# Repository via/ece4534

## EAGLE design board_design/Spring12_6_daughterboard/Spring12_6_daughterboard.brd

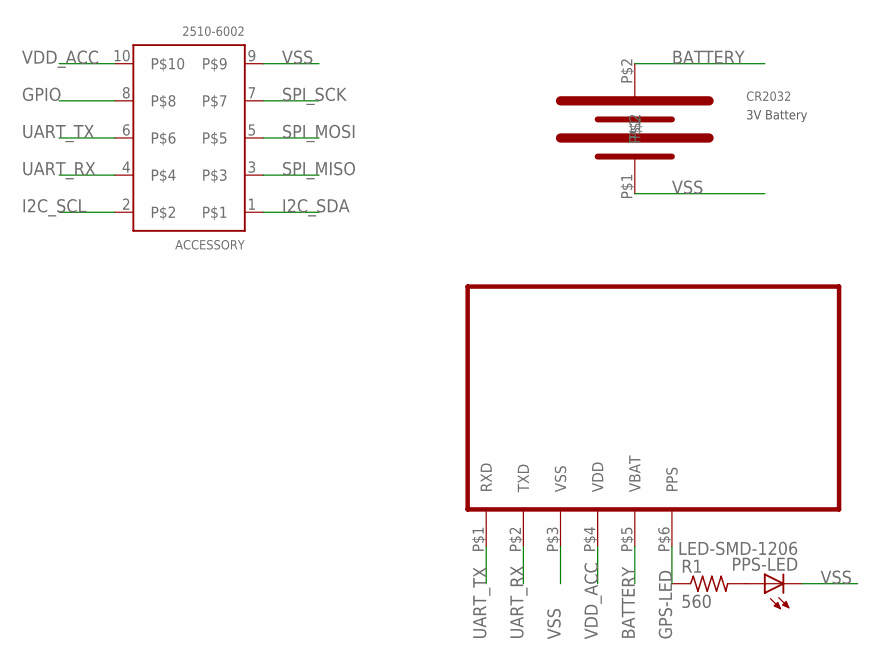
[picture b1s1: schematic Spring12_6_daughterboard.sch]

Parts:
ACCESSORY: 2510-6002
PPS-LED: LED-SMD-1206; LED1206
R1: 560; R1206
U$1: 796136-1-CR2302_HOLDER; 796136-1-CR2032_HOLDER
U$3: GPS-UP501

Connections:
BATTERY: U$1.P$2, U$3.P$5 (VBAT)
GPIO: ACCESSORY.8
GPS-LED: R1.1, U$3.P$6 (PPS)
I2C_SCL: ACCESSORY.2
I2C_SDA: ACCESSORY.1
unnamed: PPS-LED.A, R1.2
SPI_MISO: ACCESSORY.3
SPI_MOSI: ACCESSORY.5
SPI_SCK: ACCESSORY.7
UART_RX: ACCESSORY.4, U$3.P$2 (TXD)
UART_TX: ACCESSORY.6, U$3.P$1 (RXD)
VDD_ACC: ACCESSORY.10, U$3.P$4 (VDD)
VSS: ACCESSORY.9, PPS-LED.C, U$1.P$1, U$3.P$3 (VSS)

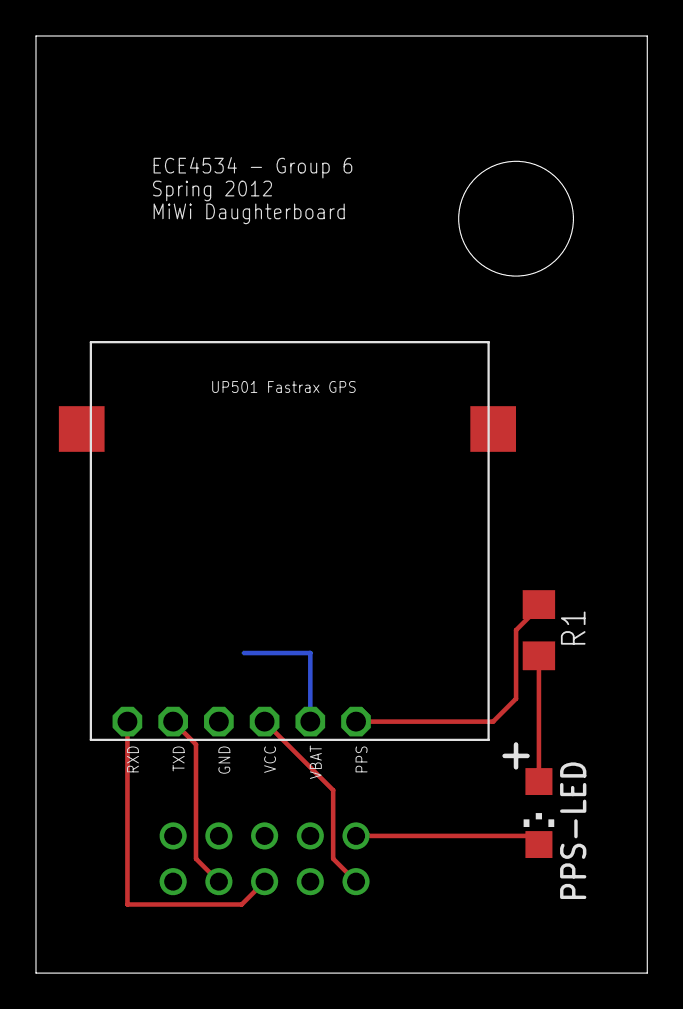
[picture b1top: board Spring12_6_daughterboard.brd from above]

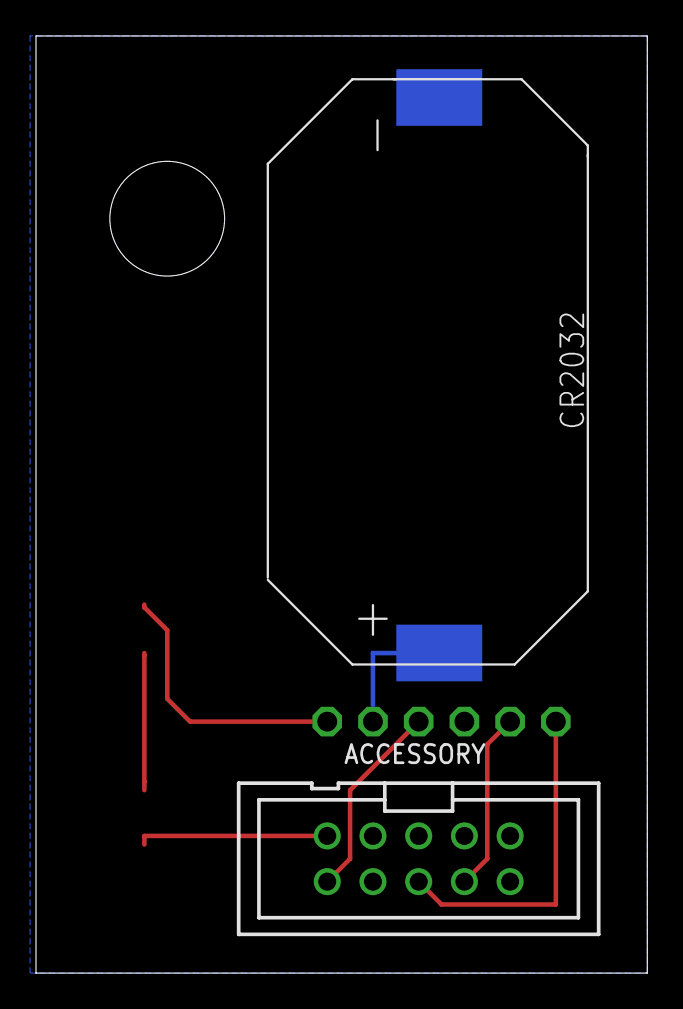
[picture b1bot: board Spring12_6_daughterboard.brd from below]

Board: 2 copper layers, 34.0 x 52.1 mm, 5 parts (2 on the bottom side), 7 nets.

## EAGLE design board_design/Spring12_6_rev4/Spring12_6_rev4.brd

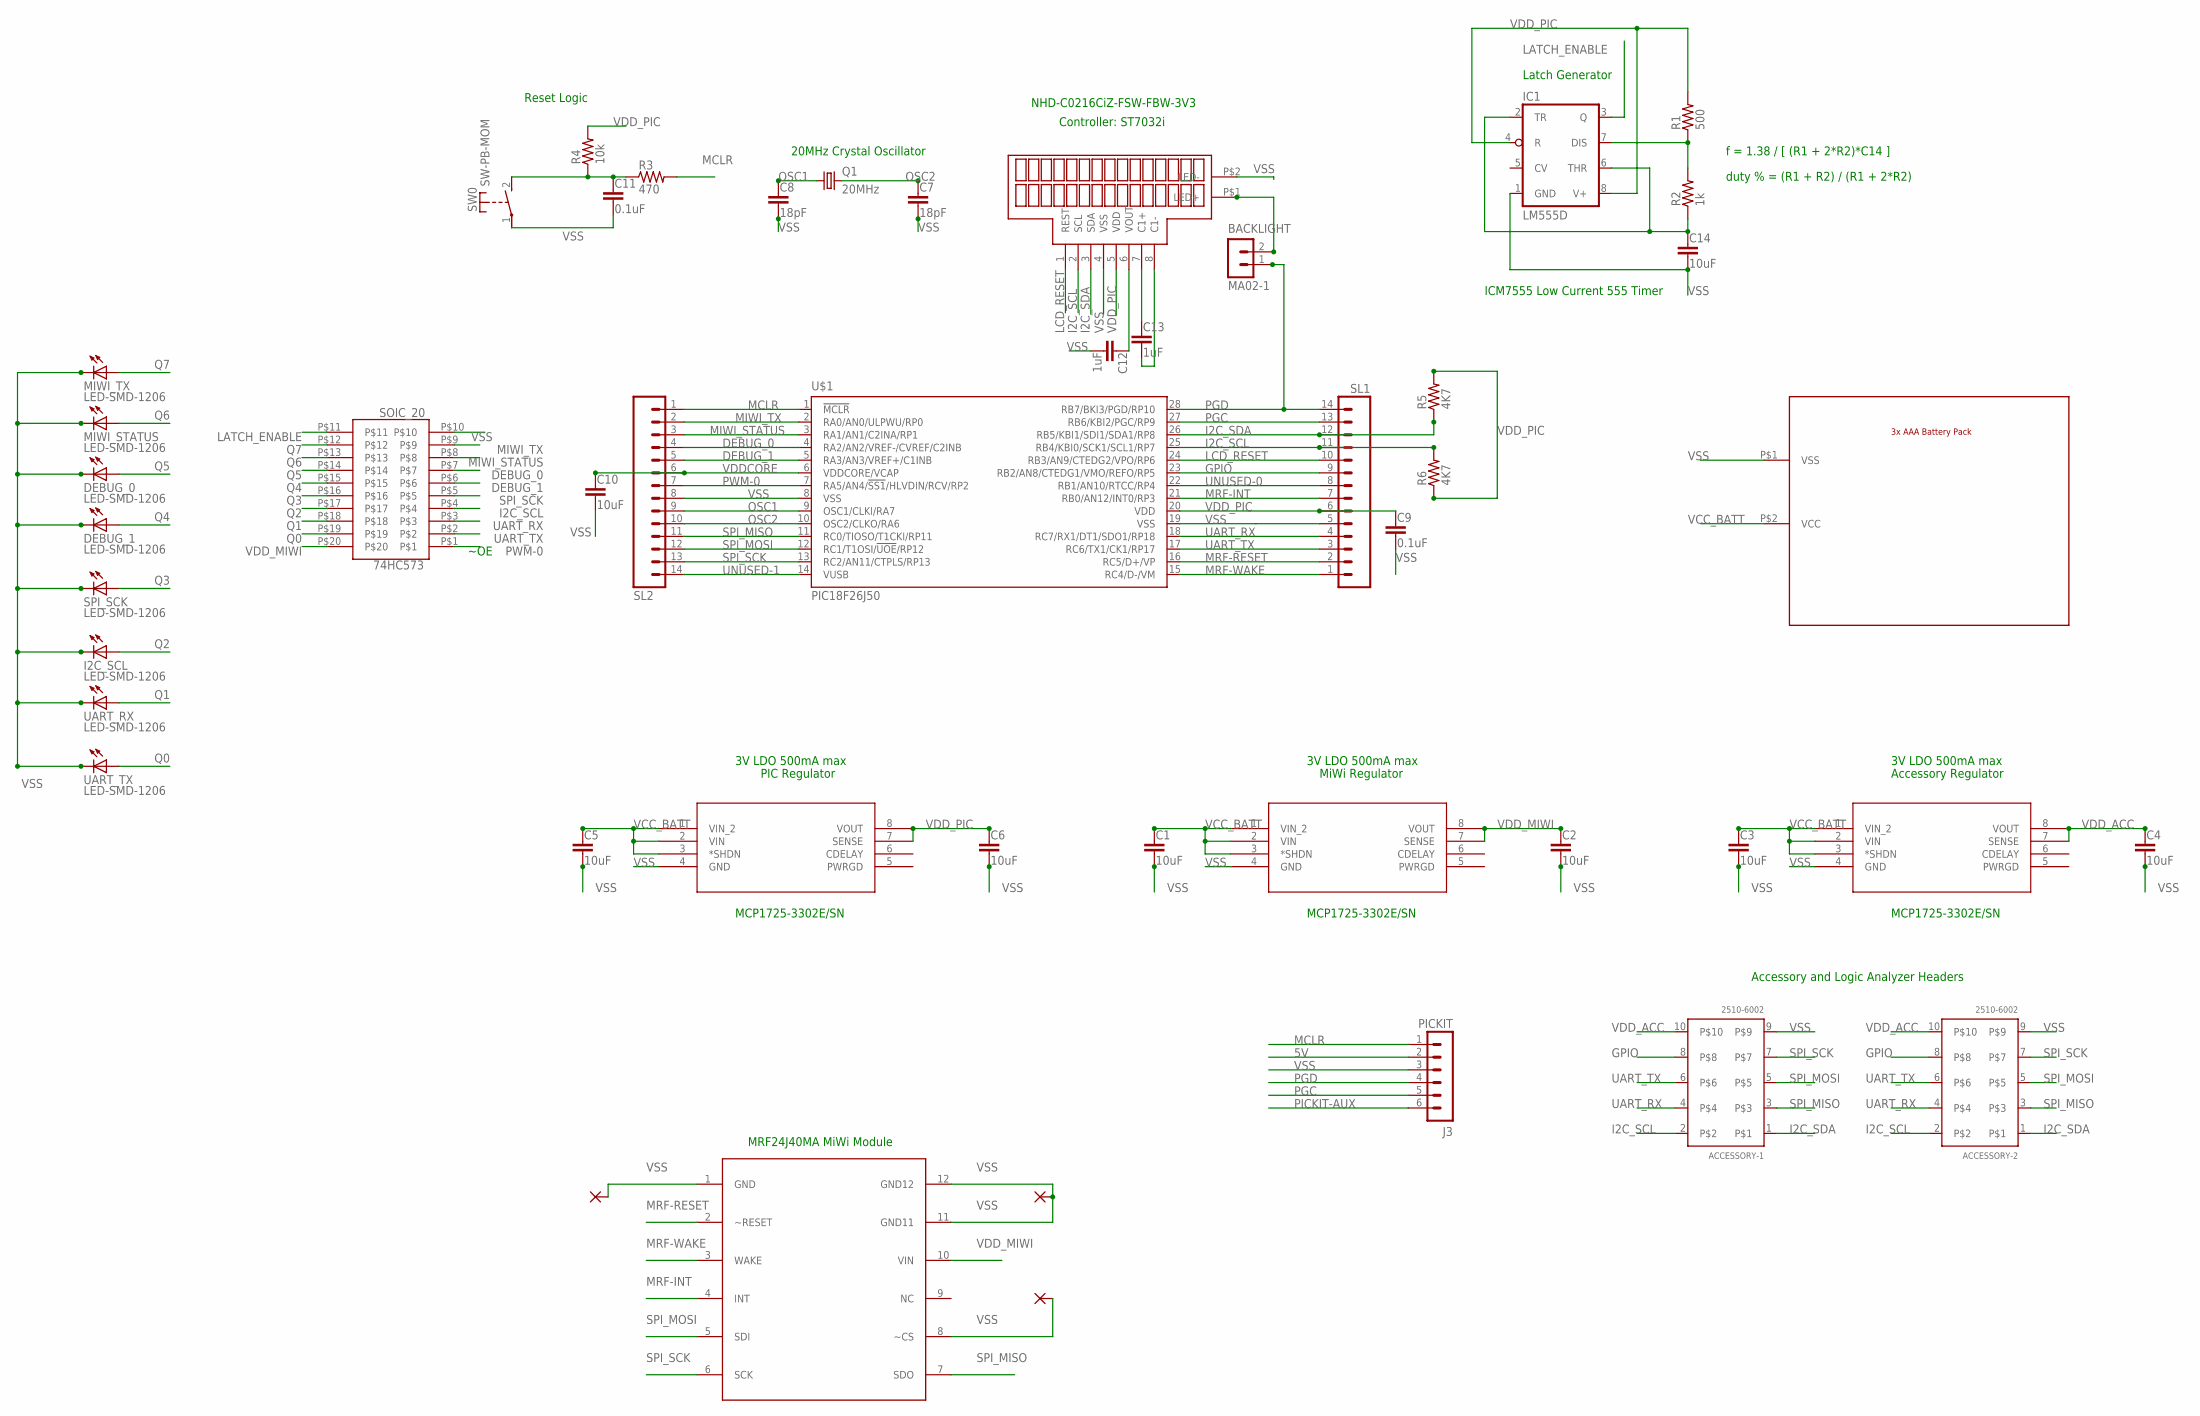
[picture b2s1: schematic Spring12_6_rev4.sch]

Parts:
74HC573: SOIC_20; SO20W
ACCESSORY-1, ACCESSORY-2: 2510-6002
BACKLIGHT: MA02-1
BATT0: 2479-BATTERY
C1, C2, C3, C4, C5, C6, C14: 10uF; C2.5-5
C7: 18pF; C2.5-5
C8: 18pF; C2.5-5; DIGIKEY 490-3632-ND
C9, C11: 0.1uF; C2.5-5; DIGIKEY 490-3632-ND
C10: 10uF; C2.5-5; DIGIKEY 490-3632-ND
C12, C13: 1uF; C2.5-5; DIGIKEY 490-3632-ND
DEBUG_0, DEBUG_1: LED-SMD-1206; LED1206
I2C_SCL: LED-SMD-1206; LED1206
IC1: LM555D; SO08
J3: PICKIT; MA06-1
MIWI_STATUS: LED-SMD-1206; LED1206
MIWI_TX: LED-SMD-1206; LED1206
Q1: 20MHz; HC49U-V; DIGIKEY XC1723-ND
R1: 500; R1206
R2: 1k; R1206
R3: 470; R1206
R4: 10k; R1206
R5, R6: 4K7; R1206
REG0, REG1, REG2: MCP1725-XXXXX/SN; SOIC8-N_MC
RF0: MRF24J40MA; PCB12
SL1, SL2: M14; 14P
SPI_SCK: LED-SMD-1206; LED1206
SW0: SW-PB-MOM; SW-MOM-PB
U$1: PIC18F26J50; DIL28-3
U$2: NHD-C0216CIZ-FN-FBW-3V; SIL8-1.5
U$18, U$19, U$20: VIA
UART_RX: LED-SMD-1206; LED1206
UART_TX: LED-SMD-1206; LED1206

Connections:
5V: J3.2
DEBUG_0: 74HC573.P$7, SL2.4, U$1.4 (RA2/AN2/VREF-/CVREF/C2INB)
DEBUG_1: 74HC573.P$6, SL2.5, U$1.5 (RA3/AN3/VREF+/C1INB)
GPIO: ACCESSORY-1.8, ACCESSORY-2.8, SL1.9, U$1.23 (RB2/AN8/CTEDG1/VMO/REFO/RP5)
I2C_SCL: 74HC573.P$4, ACCESSORY-1.2, ACCESSORY-2.2, R6.2, SL1.11, U$1.25 (RB4/KBI0/SCK1/SCL1/RP7), U$2.2 (SCL)
I2C_SDA: ACCESSORY-1.1, ACCESSORY-2.1, R5.1, SL1.12, U$1.26 (RB5/KBI1/SDI1/SDA1/RP8), U$2.3 (SDA)
LATCH_ENABLE: 74HC573.P$11, IC1.3 (Q)
LCD_RESET: SL1.10, U$1.24 (RB3/AN9/CTEDG2/VPO/RP6), U$2.1 (REST)
MCLR: J3.1, R3.2, SL2.1, U$1.1 (!MCLR)
MIWI_STATUS: 74HC573.P$8, SL2.3, U$1.3 (RA1/AN1/C2INA/RP1)
MIWI_TX: 74HC573.P$9, SL2.2, U$1.2 (RA0/AN0/ULPWU/RP0)
MRF-INT: RF0.4 (INT), SL1.7, U$1.21 (RB0/AN12/INT0/RP3)
MRF-RESET: RF0.2 (~RESET), SL1.2, U$1.16 (RC5/D+/VP)
MRF-WAKE: RF0.3 (WAKE), SL1.1, U$1.15 (RC4/D-/VM)
unnamed: BACKLIGHT.2, U$2.P$1 (LED+)
unnamed: IC1.7 (DIS), R1.1, R2.2
unnamed: C14.1, IC1.2 (TR), IC1.6 (THR), R2.1
unnamed: C11.1, R3.1, R4.1, SW0.2 (S)
unnamed: C12.1, U$2.6 (VOUT)
unnamed: C13.1, U$2.7 (C1+)
unnamed: C13.2, U$2.8 (C1-)
OSC1: C8.1, Q1.1, SL2.9, U$1.9 (OSC1/CLKI/RA7)
OSC2: C7.1, Q1.2, SL2.10, U$1.10 (OSC2/CLKO/RA6)
PGC: J3.5, SL1.13, U$1.27 (RB6/KBI2/PGC/RP9)
PGD: BACKLIGHT.1, J3.4, SL1.14, U$1.28 (RB7/BKI3/PGD/RP10)
PICKIT-AUX: J3.6
PWM-0: 74HC573.P$1, SL2.7, U$1.7 (RA5/AN4/!SS1!/HLVDIN/RCV/RP2)
Q0: 74HC573.P$19, UART_TX.A
Q1: 74HC573.P$18, UART_RX.A
Q2: 74HC573.P$17, I2C_SCL.A
Q3: 74HC573.P$16, SPI_SCK.A
Q4: 74HC573.P$15, DEBUG_1.A
Q5: 74HC573.P$14, DEBUG_0.A
Q6: 74HC573.P$13, MIWI_STATUS.A
Q7: 74HC573.P$12, MIWI_TX.A
SPI_MISO: ACCESSORY-1.3, ACCESSORY-2.3, RF0.7 (SDO), SL2.11, U$1.11 (RC0/TIOSO/T1CKI/RP11)
SPI_MOSI: ACCESSORY-1.5, ACCESSORY-2.5, RF0.5 (SDI), SL2.12, U$1.12 (RC1/T1OSI/!UOE!/RP12)
SPI_SCK: 74HC573.P$5, ACCESSORY-1.7, ACCESSORY-2.7, RF0.6 (SCK), SL2.13, U$1.13 (RC2/AN11/CTPLS/RP13)
UART_RX: 74HC573.P$3, ACCESSORY-1.4, ACCESSORY-2.4, SL1.4, U$1.18 (RC7/RX1/DT1/SDO1/RP18)
UART_TX: 74HC573.P$2, ACCESSORY-1.6, ACCESSORY-2.6, SL1.3, U$1.17 (RC6/TX1/CK1/RP17)
UNUSED-0: SL1.8, U$1.22 (RB1/AN10/RTCC/RP4)
UNUSED-1: SL2.14, U$1.14 (VUSB)
VCC_BATT: BATT0.P$2 (VCC), C1.1, C3.1, C5.1, REG0.1 (VIN_2), REG0.2 (VIN), REG0.3 (*SHDN), REG1.1 (VIN_2), REG1.2 (VIN), REG1.3 (*SHDN), REG2.1 (VIN_2), REG2.2 (VIN), REG2.3 (*SHDN)
VDDCORE: C10.1, SL2.6, U$1.6 (VDDCORE/VCAP)
VDD_ACC: ACCESSORY-1.10, ACCESSORY-2.10, C4.1, REG2.7 (SENSE), REG2.8 (VOUT)
VDD_MIWI: 74HC573.P$20, C2.1, REG1.7 (SENSE), REG1.8 (VOUT), RF0.10 (VIN)
VDD_PIC: C6.1, C9.1, IC1.4 (R), IC1.8 (V+), R1.2, R4.2, R5.2, R6.1, REG0.7 (SENSE), REG0.8 (VOUT), SL1.6, U$1.20 (VDD), U$2.5 (VDD)
VSS: 74HC573.P$10, ACCESSORY-1.9, ACCESSORY-2.9, BATT0.P$1 (VSS), C1.2, C2.2, C3.2, C4.2, C5.2, C6.2, C7.2, C8.2, C9.2, C10.2, C11.2, C12.2, C14.2, DEBUG_0.C, DEBUG_1.C, I2C_SCL.C, IC1.1 (GND), J3.3, MIWI_STATUS.C, MIWI_TX.C, REG0.4 (GND), REG1.4 (GND), REG2.4 (GND), RF0.1 (GND), RF0.8 (~CS), RF0.11 (GND11), RF0.12 (GND12), SL1.5, SL2.8, SPI_SCK.C, SW0.1, U$1.8 (VSS), U$1.19 (VSS), U$2.4 (VSS), U$2.P$2 (LED-), U$18.1, U$19.1, U$20.1, UART_RX.C, UART_TX.C

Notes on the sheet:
3V LDO 500mA max
MCP1725-3302E/SN
PIC Regulator
MiWi Regulator
Accessory Regulator
20MHz Crystal Oscillator
Accessory and Logic Analyzer Headers
Reset Logic
NHD-C0216CiZ-FSW-FBW-3V3
Controller: ST7032i
MRF24J40MA MiWi Module
Latch Generator
ICM7555 Low Current 555 Timer
f = 1.38 / [ (R1 + 2*R2)*C14 ]
duty % = (R1 + R2) / (R1 + 2*R2)
~OE

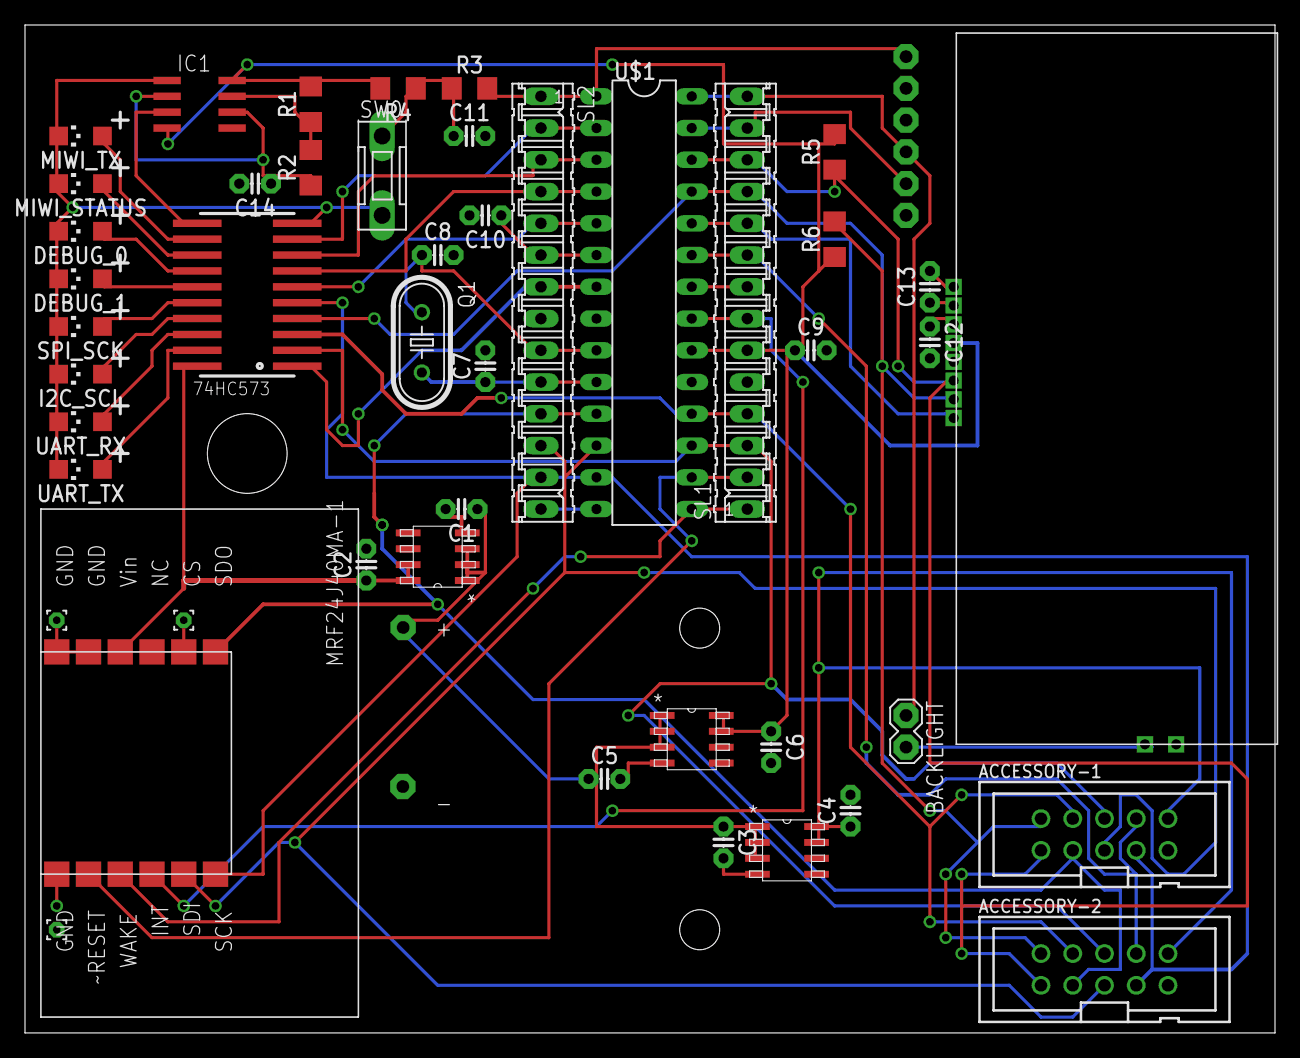
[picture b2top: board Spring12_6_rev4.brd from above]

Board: 2 copper layers, 100.0 x 80.6 mm, 48 parts (1 on the bottom side), 46 nets.

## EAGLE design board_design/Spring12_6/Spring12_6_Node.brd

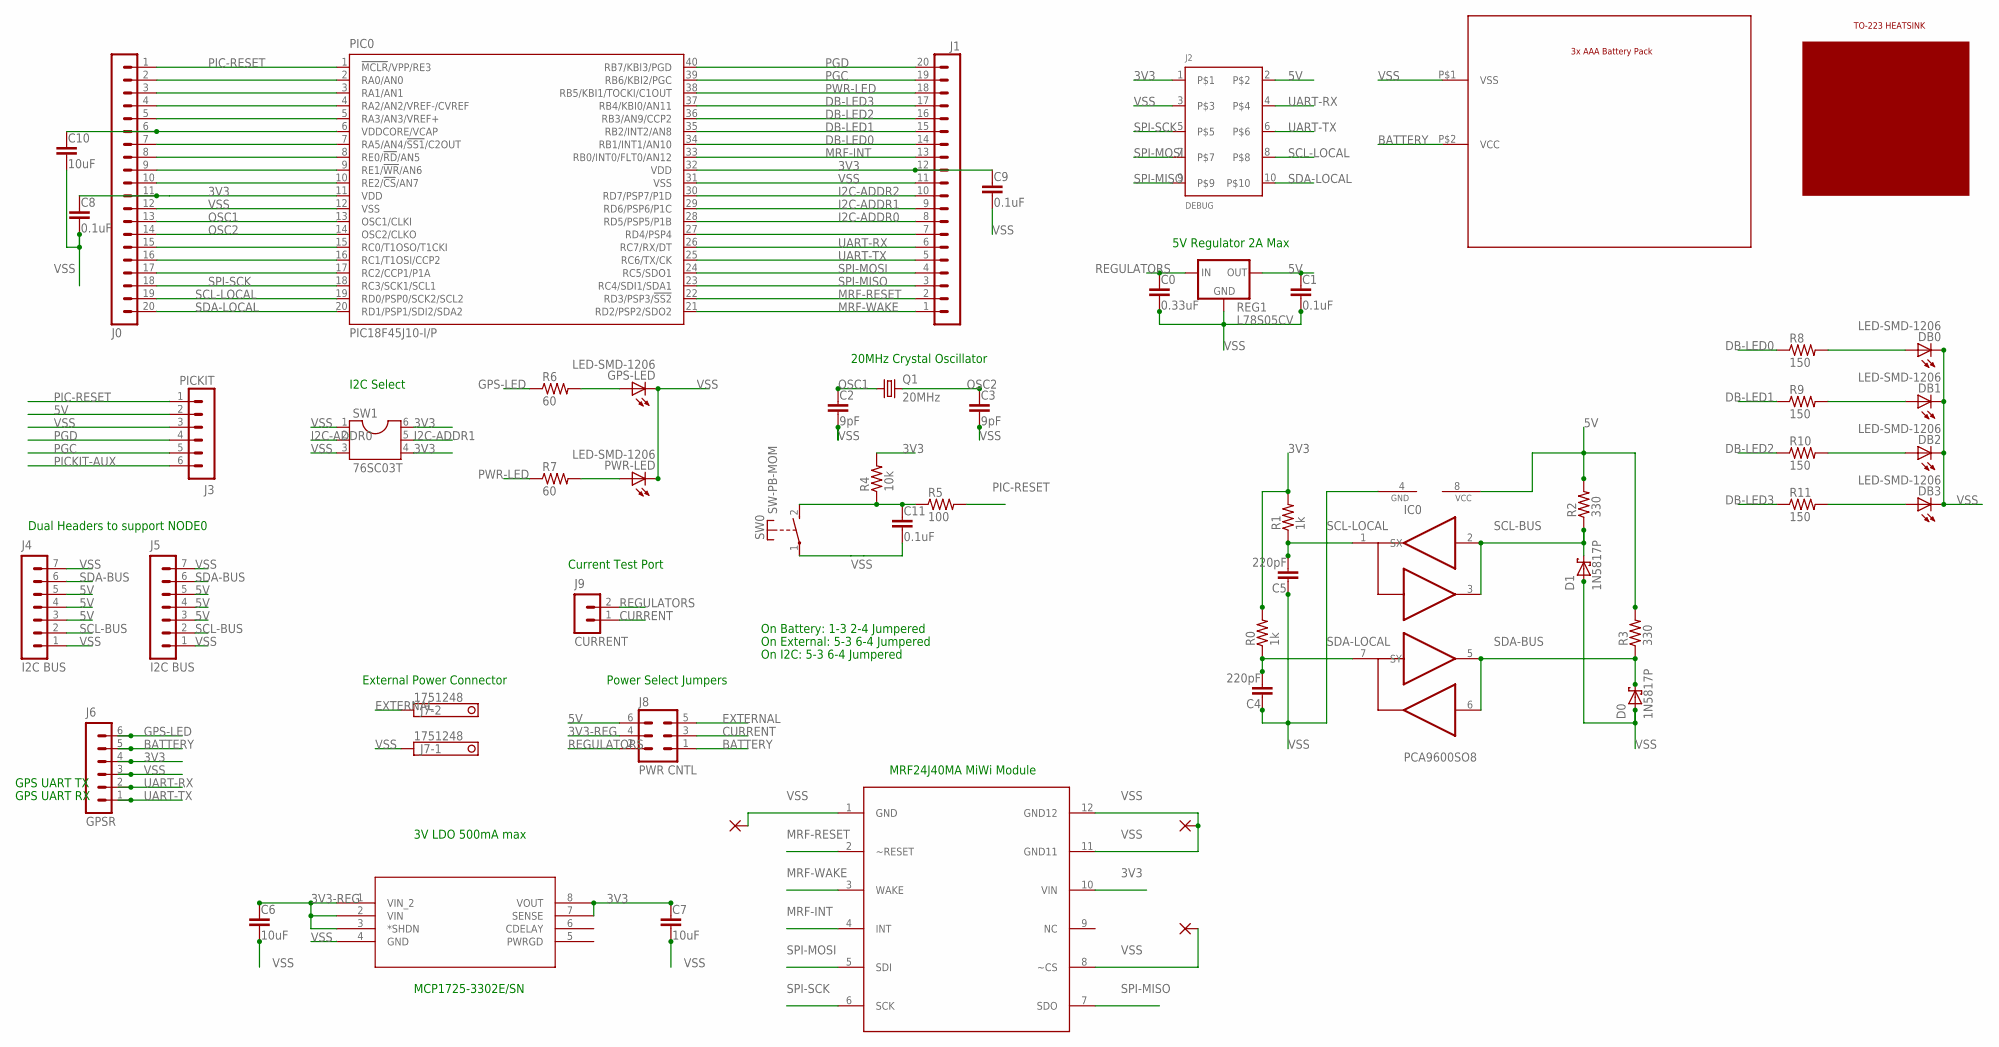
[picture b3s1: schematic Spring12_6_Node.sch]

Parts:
BATT0: 2479-BATTERY
C0: 0.33uF; C2.5-5
C1: 0.1uF; C2.5-5
C2: 9pF; C2.5-5; DIGIKEY 490-3632-ND
C3: 9pF; C2.5-5
C4, C5: 220pF; C2.5-5
C6, C7: 10uF; C2.5-5
C8, C9, C11: 0.1uF; C2.5-5; DIGIKEY 490-3632-ND
C10: 10uF; C2.5-5; DIGIKEY 490-3632-ND
D0, D1: 1N5817P; 1N5817
DB0, DB1, DB2, DB3: LED-SMD-1206; LED1206
GPS-LED: LED-SMD-1206; LED1206
IC0: PCA9600SO8; SO08
J0, J1: MA20-1
J2: DEBUG; 2510-6002
J3: PICKIT; MA06-1
J4, J5: I2C BUS; MA07-1
J6: GPSR; MA06-1
J7: 1751248
J8: PWR CNTL; MA03-2
J9: CURRENT; MA02-1
PIC0: PIC18F45J10-I/P; DIL40
PWR-LED: LED-SMD-1206; LED1206
Q1: 20MHz; HC49U-V; DIGIKEY XC1723-ND
R0, R1: 1k; R-1/4W
R2, R3: 330; R-1/4W
R4: 10k; R1206
R5: 100; R1206
R6, R7: 60; R1206
R8, R9, R10, R11: 150; R1206
REG0: MCP1725-XXXXX/SN; SOIC8-N_MC
REG1: L78S05CV; 78XXL
RF0: MRF24J40MA; PCB12
SW0: SW-PB-MOM; SW-MOM-PB
SW1: 76SC03T; DIL06
U$18, U$19, U$20: VIA
U$28: 7-361-BA

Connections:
3V3: C7.1, C8.1, C9.1, J0.11, J1.12, J2.1, J6.4, PIC0.11 (VDD), PIC0.32 (VDD), R0.2, R1.2, R4.2, REG0.7 (SENSE), REG0.8 (VOUT), RF0.10 (VIN), SW1.4, SW1.6
3V3-REG: C6.1, J8.4, REG0.1 (VIN_2), REG0.2 (VIN), REG0.3 (*SHDN)
5V: C1.1, IC0.8 (VCC), J2.2, J3.2, J4.3, J4.4, J4.5, J5.3, J5.4, J5.5, J8.6, R2.2, R3.2, REG1.OUT
BATTERY: BATT0.P$2 (VCC), J6.5, J8.1
CURRENT: J8.3, J9.1
DB-LED0: J1.14, PIC0.34 (RB1/INT1/AN10), R8.1
DB-LED1: J1.15, PIC0.35 (RB2/INT2/AN8), R9.1
DB-LED2: J1.16, PIC0.36 (RB3/AN9/CCP2), R10.1
DB-LED3: J1.17, PIC0.37 (RB4/KBI0/AN11), R11.1
EXTERNAL: J7.2, J8.5
GPS-LED: J6.6, R6.1
I2C-ADDR0: J1.8, PIC0.28 (RD5/PSP5/P1B), SW1.2
I2C-ADDR1: J1.9, PIC0.29 (RD6/PSP6/P1C), SW1.5
I2C-ADDR2: J1.10, PIC0.30 (RD7/PSP7/P1D)
MRF-INT: J1.13, PIC0.33 (RB0/INT0/FLT0/AN12), RF0.4 (INT)
MRF-RESET: J1.2, PIC0.22 (RD3/PSP3/!SS2!), RF0.2 (~RESET)
MRF-WAKE: J1.1, PIC0.21 (RD2/PSP2/SDO2), RF0.3 (WAKE)
unnamed: J0.8, PIC0.8 (RE0/!RD!/AN5)
unnamed: J0.15, PIC0.15 (RC0/T1OSO/T1CKI)
unnamed: J0.16, PIC0.16 (RC1/T1OSI/CCP2)
unnamed: GPS-LED.A, R6.2
unnamed: PWR-LED.A, R7.2
unnamed: C11.1, R4.1, R5.1, SW0.2 (S)
unnamed: DB0.A, R8.2
unnamed: J1.7, PIC0.27 (RD4/PSP4)
unnamed: DB1.A, R9.2
unnamed: DB2.A, R10.2
unnamed: DB3.A, R11.2
unnamed: J0.2, PIC0.2 (RA0/AN0)
unnamed: J0.3, PIC0.3 (RA1/AN1)
unnamed: J0.4, PIC0.4 (RA2/AN2/VREF-/CVREF)
unnamed: J0.5, PIC0.5 (RA3/AN3/VREF+)
unnamed: C10.1, J0.6, PIC0.6 (VDDCORE/VCAP)
unnamed: J0.7, PIC0.7 (RA5/AN4/!SS1!/C2OUT)
unnamed: J0.9, PIC0.9 (RE1/!WR!/AN6)
unnamed: J0.10, PIC0.10 (RE2/!CS!/AN7)
unnamed: J0.17, PIC0.17 (RC2/CCP1/P1A)
OSC1: C2.1, J0.13, PIC0.13 (OSC1/CLKI), Q1.1
OSC2: C3.1, J0.14, PIC0.14 (OSC2/CLKO), Q1.2
PGC: J1.19, J3.5, PIC0.39 (RB6/KBI2/PGC)
PGD: J1.20, J3.4, PIC0.40 (RB7/KBI3/PGD)
PIC-RESET: J0.1, J3.1, PIC0.1 (!MCLR!/VPP/RE3), R5.2
PICKIT-AUX: J3.6
PWR-LED: J1.18, PIC0.38 (RB5/KBI1/TOCKI/C1OUT), R7.1
REGULATORS: C0.1, J8.2, J9.2, REG1.IN
SCL-BUS: D1.C, IC0.2 (RX), IC0.3 (TX), J4.2, J5.2, R2.1
SCL-LOCAL: C5.2, IC0.1 (SX), J0.19, J2.8, PIC0.19 (RD0/PSP0/SCK2/SCL2), R1.1
SDA-BUS: D0.C, IC0.5 (TY), IC0.6 (RY), J4.6, J5.6, R3.1
SDA-LOCAL: C4.2, IC0.7 (SY), J0.20, J2.10, PIC0.20 (RD1/PSP1/SDI2/SDA2), R0.1
SPI-MISO: J1.3, J2.9, PIC0.23 (RC4/SDI1/SDA1), RF0.7 (SDO)
SPI-MOSI: J1.4, J2.7, PIC0.24 (RC5/SDO1), RF0.5 (SDI)
SPI-SCK: J0.18, J2.5, PIC0.18 (RC3/SCK1/SCL1), RF0.6 (SCK)
UART-RX: J1.6, J2.4, J6.2, PIC0.26 (RC7/RX/DT)
UART-TX: J1.5, J2.6, J6.1, PIC0.25 (RC6/TX/CK)
VSS: BATT0.P$1 (VSS), C0.2, C1.2, C2.2, C3.2, C4.1, C5.1, C6.2, C7.2, C8.2, C9.2, C10.2, C11.2, D0.A, D1.A, DB0.C, DB1.C, DB2.C, DB3.C, GPS-LED.C, IC0.4 (GND), J0.12, J1.11, J2.3, J3.3, J4.1, J4.7, J5.1, J5.7, J6.3, J7.1, PIC0.12 (VSS), PIC0.31 (VSS), PWR-LED.C, REG0.4 (GND), REG1.GND, RF0.1 (GND), RF0.8 (~CS), RF0.11 (GND11), RF0.12 (GND12), SW0.1, SW1.1, SW1.3, U$18.1, U$19.1, U$20.1

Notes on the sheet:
3V LDO 500mA max
MCP1725-3302E/SN
GPS UART TX
GPS UART RX
20MHz Crystal Oscillator
MRF24J40MA MiWi Module
External Power Connector
Power Select Jumpers
Current Test Port
Dual Headers to support NODE0
5V Regulator 2A Max
On Battery: 1-3 2-4 Jumpered
On External: 5-3 6-4 Jumpered
On I2C: 5-3 6-4 Jumpered
I2C Select

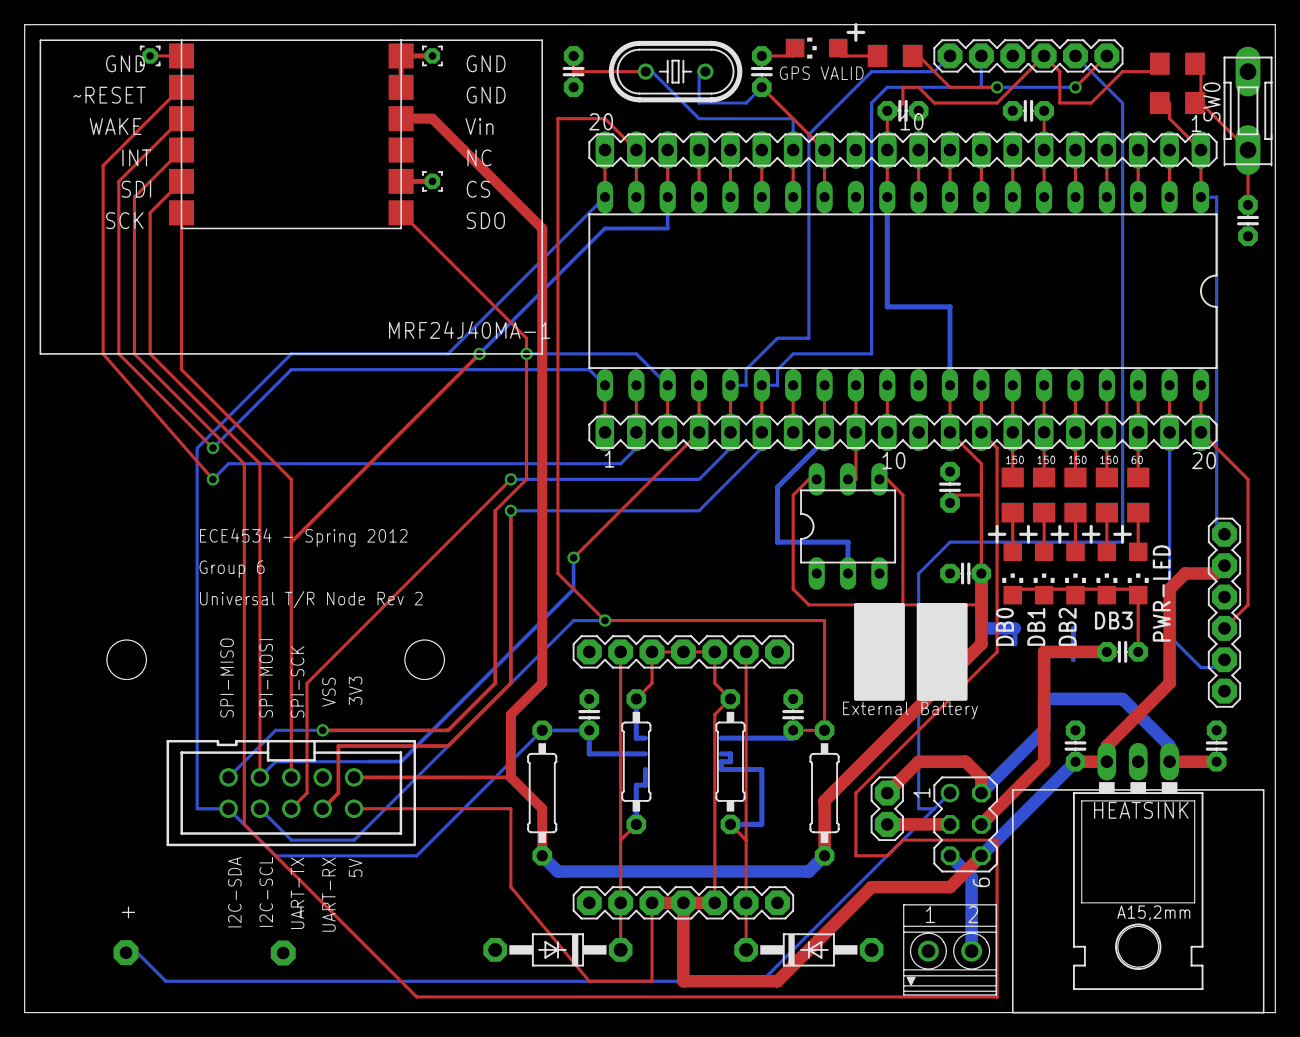
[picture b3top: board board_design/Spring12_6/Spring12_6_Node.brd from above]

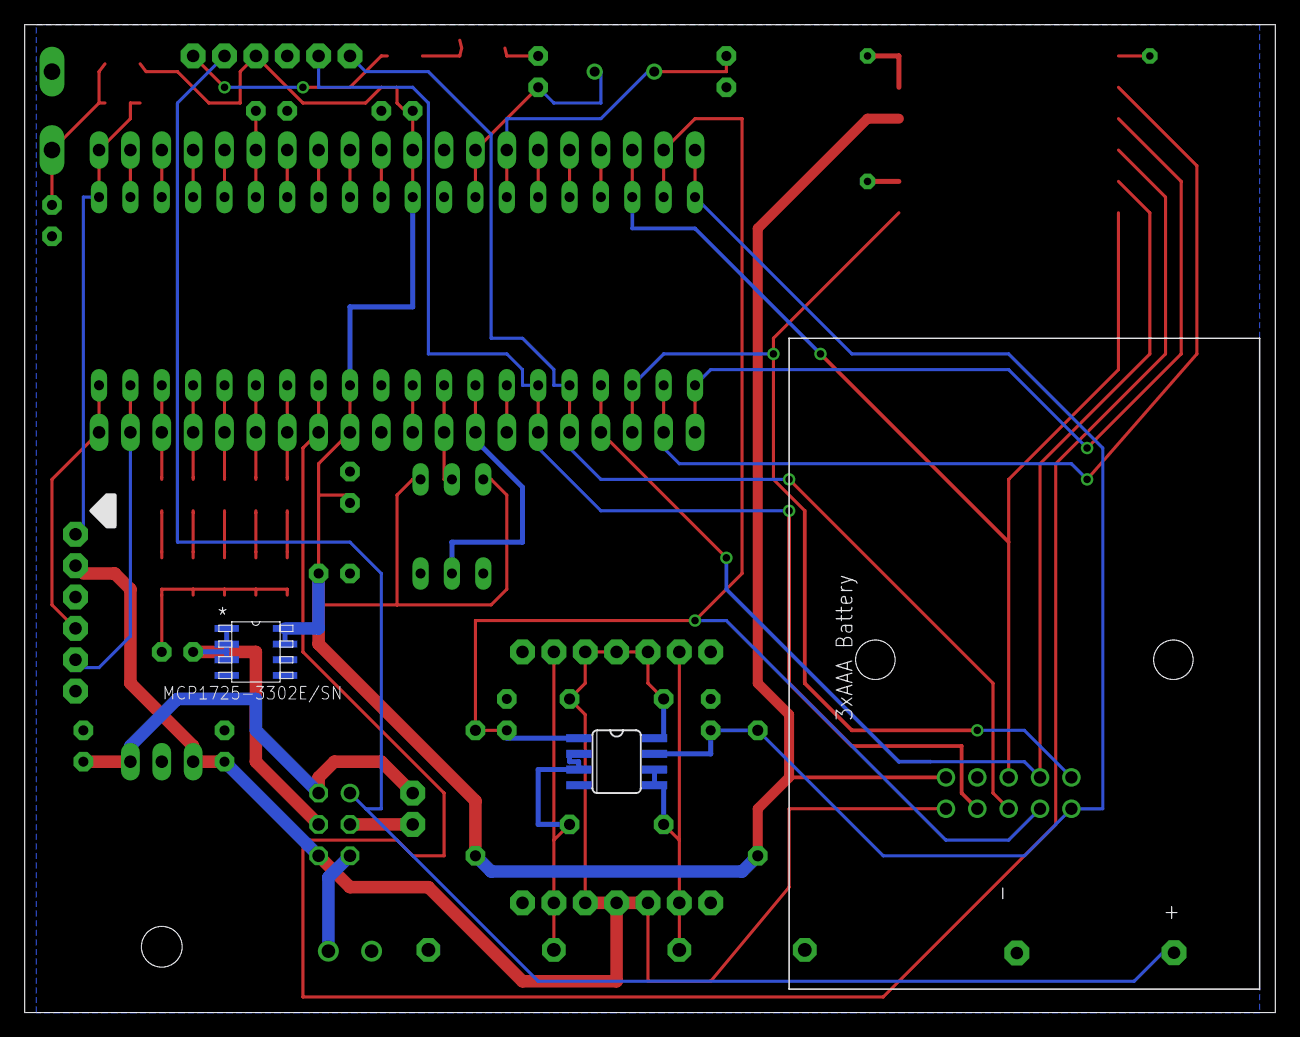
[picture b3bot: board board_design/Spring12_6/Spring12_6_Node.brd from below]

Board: 2 copper layers, 101.3 x 80.0 mm, 55 parts (2 on the bottom side), 54 nets.

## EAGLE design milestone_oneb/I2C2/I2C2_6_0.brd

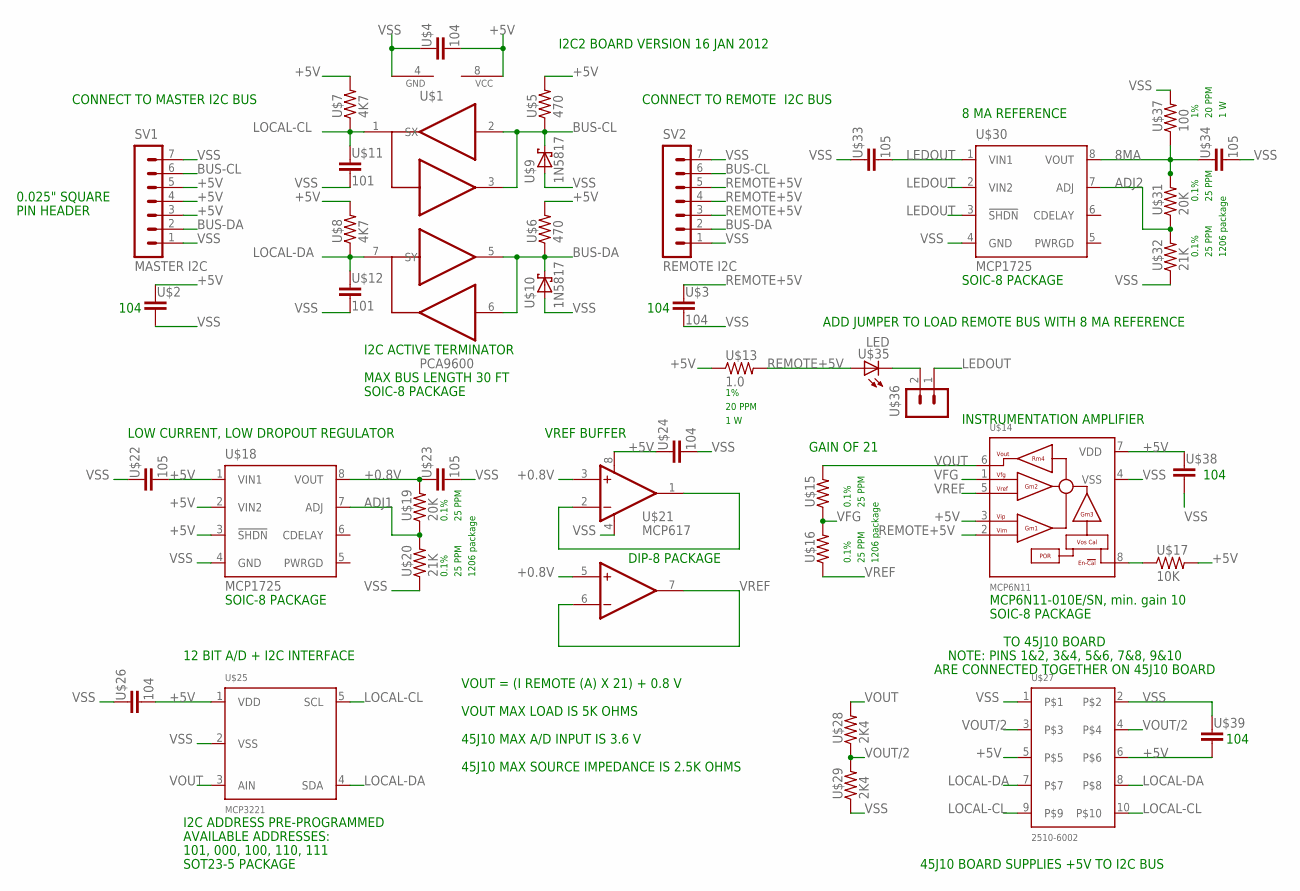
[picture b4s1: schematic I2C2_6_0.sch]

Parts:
SV1: MASTER I2C; MA07-1
SV2: REMOTE I2C; MA07-1
U$1: PCA9600; SO08
U$2, U$38, U$39: C2.5-5
U$3, U$4, U$24, U$26: 104; C2.5-5
U$5, U$6: 470; R-1/4W
U$7, U$8: 4K7; R-1/4W
U$9, U$10: 1N5817
U$11, U$12: 101; C2.5-5
U$13: 1.0; R-1W
U$14: MCP6N11; SO08
U$15, U$16: R1206
U$17: 10K; R-1/4W
U$18, U$30: MCP1725; SO08
U$19, U$31: 20K; R1206
U$20, U$32: 21K; R1206
U$21: MCP617; DIL08
U$22, U$23, U$33, U$34: 105; C2.5-5
U$25: MCP3221; SOT23-5
U$27: 2510-6002
U$28, U$29: 2K4; R-1/4W
U$35: LED; LED1206
U$36: MA02-1
U$37: 100; R-1W

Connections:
8MA: U$30.8 (VOUT), U$31.2, U$34.1, U$37.1
+0.8V: U$18.8 (VOUT), U$19.2, U$21.3 (+IN), U$21.5 (+IN1), U$23.1
+5V: SV1.3, SV1.4, SV1.5, U$1.8 (VCC), U$2.1, U$4.2, U$5.2, U$6.2, U$7.2, U$8.2, U$13.1, U$14.3 (VIP), U$14.7 (VDD), U$17.2, U$18.1 (VIN1), U$18.2 (VIN2), U$18.3 (!SHDN), U$21.8 (V+), U$22.2, U$24.1, U$25.1 (VDD), U$26.2, U$27.5, U$27.6, U$38.1, U$39.2
ADJ1: U$18.7 (ADJ), U$19.1, U$20.2
ADJ2: U$30.7 (ADJ), U$31.1, U$32.2
BUS-CL: SV1.6, SV2.6, U$1.2 (RX), U$1.3 (TX), U$5.1, U$9.C
BUS-DA: SV1.2, SV2.2, U$1.5 (TY), U$1.6 (RY), U$6.1, U$10.C
LEDOUT: U$30.1 (VIN1), U$30.2 (VIN2), U$30.3 (!SHDN), U$33.2, U$36.1
LOCAL-CL: U$1.1 (SX), U$7.1, U$11.1, U$25.5 (SCL), U$27.9, U$27.10
LOCAL-DA: U$1.7 (SY), U$8.1, U$12.1, U$25.4 (SDA), U$27.7, U$27.8
unnamed: U$35.C, U$36.2
unnamed: U$14.8 (EN), U$17.1
REMOTE+5V: SV2.3, SV2.4, SV2.5, U$3.1, U$13.2, U$14.2 (VIM), U$35.A
VFG: U$14.1 (VFG), U$15.1, U$16.2
VOUT: U$14.6 (VOUT), U$15.2, U$25.3 (AIN), U$28.2
VOUT/2: U$27.3, U$27.4, U$28.1, U$29.2
VREF: U$14.5 (VREF), U$16.1, U$21.6 (-IN1), U$21.7 (OUT1)
VREF2: U$21.1 (OUT), U$21.2 (-IN)
VSS: SV1.1, SV1.7, SV2.1, SV2.7, U$1.4 (GND), U$2.2, U$3.2, U$4.1, U$9.A, U$10.A, U$11.2, U$12.2, U$14.4 (VSS), U$18.4 (GND), U$20.1, U$21.4 (V-), U$22.1, U$23.2, U$24.2, U$25.2 (VSS), U$26.1, U$27.1, U$27.2, U$29.1, U$30.4 (GND), U$32.1, U$33.1, U$34.2, U$37.2, U$38.2, U$39.1

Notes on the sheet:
GAIN OF 21
MCP6N11-010E/SN, min. gain 10
0.1%
20 PPM
25 PPM
ADD JUMPER TO LOAD REMOTE BUS WITH 8 MA REFERENCE
1 W
VOUT = (I REMOTE (A) X 21) + 0.8 V
45J10 MAX A/D INPUT IS 3.6 V
VOUT MAX LOAD IS 5K OHMS
45J10 MAX SOURCE IMPEDANCE IS 2.5K OHMS
TO 45J10 BOARD
CONNECT TO MASTER I2C BUS
CONNECT TO REMOTE I2C BUS
8 MA REFERENCE
INSTRUMENTATION AMPLIFIER
LOW CURRENT, LOW DROPOUT REGULATOR
VREF BUFFER
12 BIT A/D + I2C INTERFACE
I2C ADDRESS PRE-PROGRAMMED
AVAILABLE ADDRESSES:
101, 000, 100, 110, 111
I2C ACTIVE TERMINATOR
MAX BUS LENGTH 30 FT
I2C2 BOARD VERSION 16 JAN 2012
NOTE: PINS 1&2, 3&4, 5&6, 7&8, 9&10
ARE CONNECTED TOGETHER ON 45J10 BOARD
45J10 BOARD SUPPLIES +5V TO I2C BUS
SOIC-8 PACKAGE
SOT23-5 PACKAGE
DIP-8 PACKAGE
0.025" SQUARE
PIN HEADER
1206 package
104

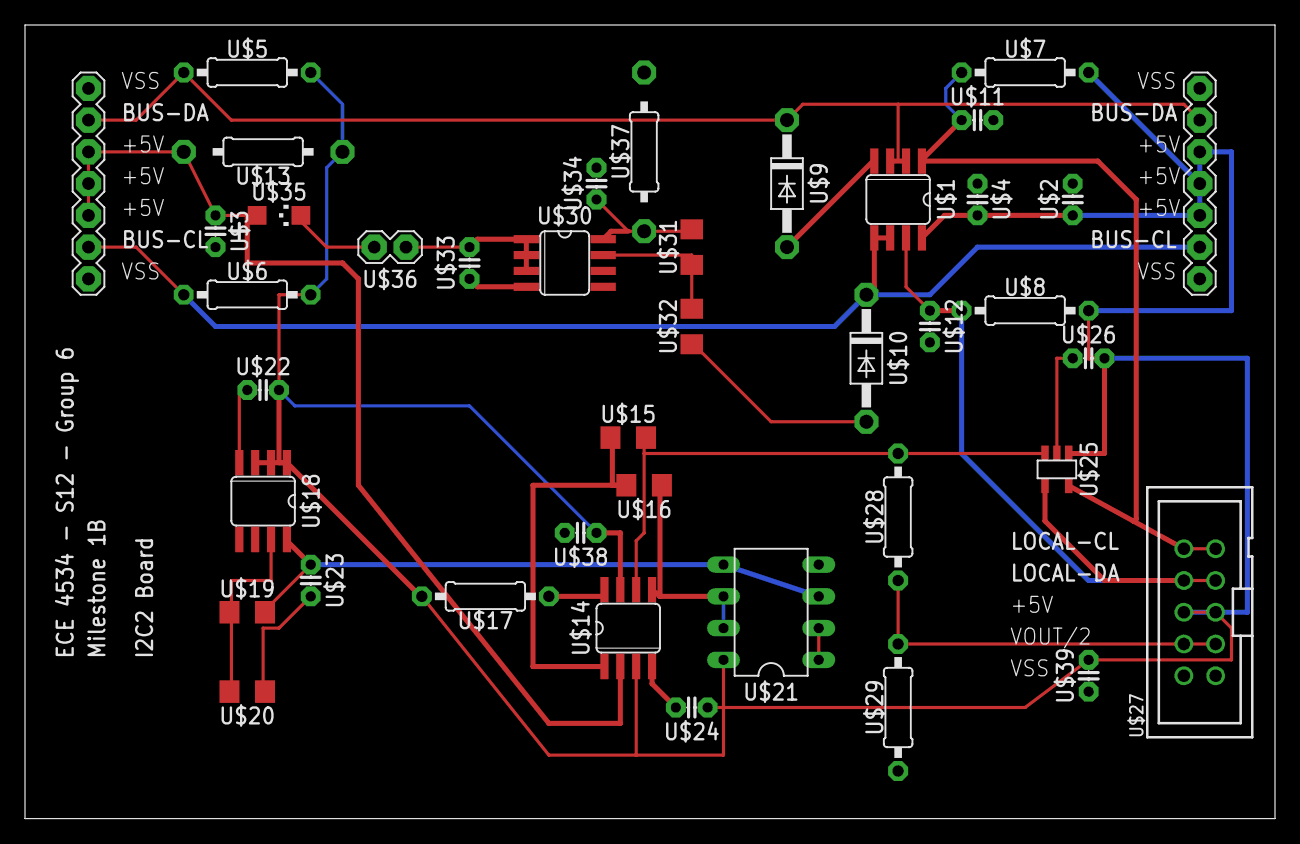
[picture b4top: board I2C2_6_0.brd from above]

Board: 2 copper layers, 100.0 x 63.5 mm, 41 parts (0 on the bottom side), 19 nets.

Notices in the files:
parts and their libraries:
SparkFun: Licensing: CC v3.0 Share-Alike You are welcome to use this library for commercial purposes.
